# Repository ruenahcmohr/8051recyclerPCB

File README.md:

# 8051recyclerPCB
External memory card for PLCC 8051 OTP processors

PCB designed for recycling OTP PLCC 8051 chips. 

Becasue using the 8051 with external memory burns off most of the ports, I have added two chips that use the external RAM space for an input and output port. Any write to external memory will go to the dedicated output port, and any read from external memory will read the dedicated input port.

(I hope your fine with the in-chip ram :] )

ERATTA:

- The output chip needs to be 74xx374 or another pin compatible chip but sure the heck not the 74xx373
- Oh, maybe those serial leds ought to be active low eh?
- Ya know that trace to that top decoupling cap dunn't need to be only 10 thou.

IMPROVA:

- Could there please be a mark on the common cathode pin of that damn led?
- Could someone please mark the xtal pin for extern clock input?
- Ya know that trace to that top decoupling cap dunn't need to be only 10 thou.
- break out pins 1, 12, 23, 34 to pads incase they need bodge connections
- align the pin 27 connection with VCC for easier bridging to use 2764 roms. (haha wait no, there are only 28 pins)

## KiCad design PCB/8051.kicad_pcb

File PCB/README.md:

# 8051recyclerPCB
External memory card for PLCC 8051 OTP processors

PCB designed for recycling OTP PLCC 8051 chips. 

Becasue using the 8051 with external memory burns off most of the ports, I have added two chips that use the external RAM space for an input and output port. Any write to external memory will go to the dedicated output port, and any read from external memory will read the dedicated input port.

(I hope your fine with the in-chip ram :] )

*not tested yet (oct 2024) *

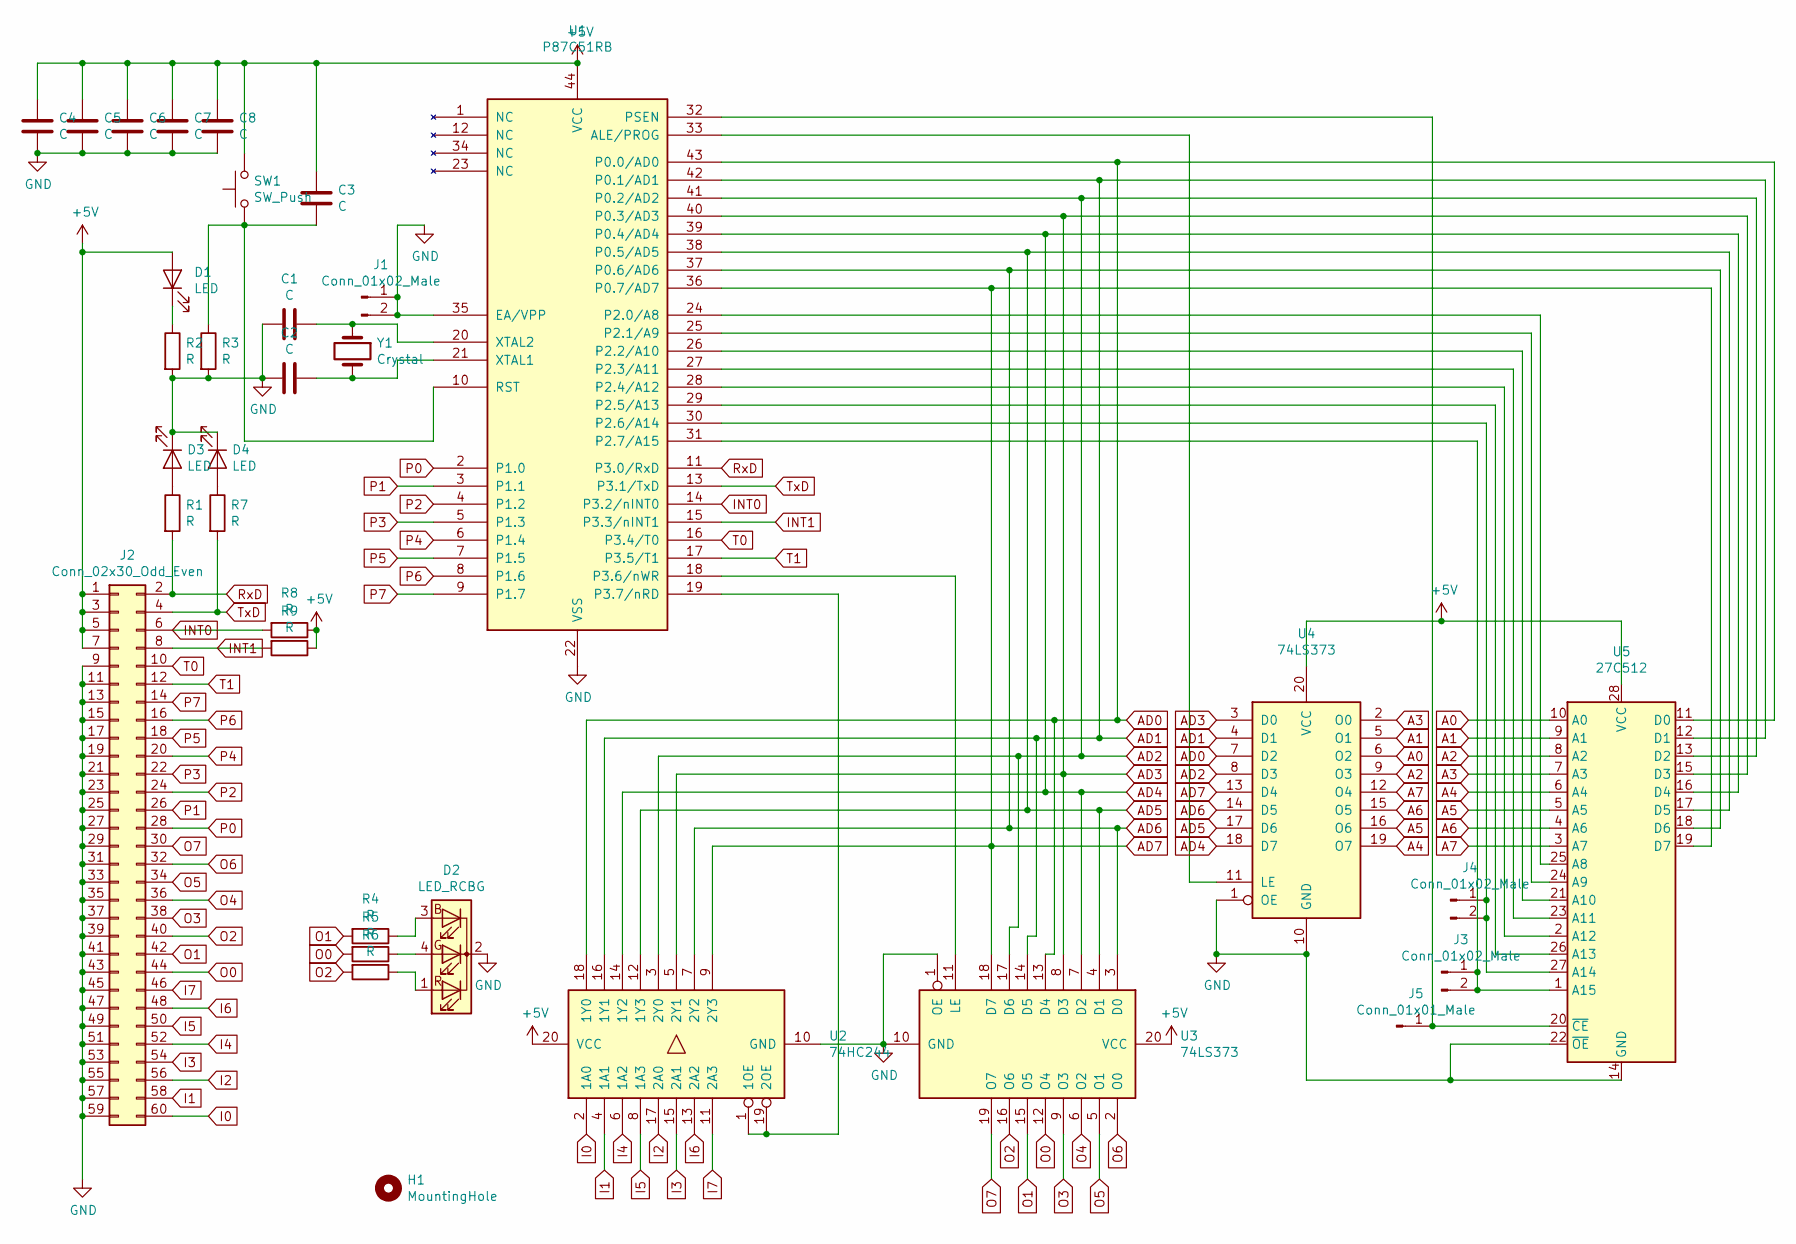
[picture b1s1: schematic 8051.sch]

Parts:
C1, C2: C; C_0805_2012Metric_Pad1.15x1.40mm_HandSolder
C3, C4, C5, C6, C7, C8: C; C_1206_3216Metric_Pad1.42x1.75mm_HandSolder
D1, D3, D4: LED; LED_0805_2012Metric_Pad1.15x1.40mm_HandSolder
D2: LED_RCBG; LED_D5.0mm-4_RGB_Wide_Pins
H1: MountingHole; MountingHole_3.2mm_M3
J1, J3, J4: Conn_01x02_Male; PinSocket_1x02_P2.54mm_Vertical
J2: Conn_02x30_Odd_Even; PinHeader_2x30_P2.54mm_Vertical
J5: Conn_01x01_Male; PinSocket_1x01_P2.54mm_Vertical
R1, R2, R3, R4, R5, R6, R7, R8, R9: R; R_0805_2012Metric_Pad1.15x1.40mm_HandSolder
SW1: SW_Push; SW_PUSH_6mm
U1: P87C51RB; PLCC-44
U2: 74HC244; SOIC-20W_7.5x12.8mm_P1.27mm
U3, U4: 74LS373; SOIC-20W_7.5x12.8mm_P1.27mm
U5: 27C512; DIP-28_W15.24mm
Y1: Crystal; Crystal_HC49-4H_Vertical

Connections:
+5V: C3.1, C4.1, C5.1, C6.1, C7.1, C8.1, D1.2 (A), J2.1, J2.3, J2.5, J2.7, R8.1, R9.1, SW1.1, U1.44 (VCC), U2.20 (VCC), U3.20 (VCC), U4.20 (VCC), U5.28 (VCC)
A0: U4.6 (O2), U5.10 (A0)
A1: U4.5 (O1), U5.9 (A1)
A2: U4.9 (O3), U5.8 (A2)
A3: U4.2 (O0), U5.7 (A3)
A4: U4.19 (O7), U5.6 (A4)
A5: U4.16 (O6), U5.5 (A5)
A6: U4.15 (O5), U5.4 (A6)
A7: U4.12 (O4), U5.3 (A7)
AD0: U1.43 (P0.0/AD0), U2.18 (1Y0), U3.13 (D4), U4.7 (D2), U5.11 (D0)
AD1: U1.42 (P0.1/AD1), U2.16 (1Y1), U3.14 (D5), U4.4 (D1), U5.12 (D1)
AD2: U1.41 (P0.2/AD2), U2.3 (2Y0), U3.17 (D6), U4.8 (D3), U5.13 (D2)
AD3: U1.40 (P0.3/AD3), U2.5 (2Y1), U3.8 (D3), U4.3 (D0), U5.15 (D3)
AD4: U1.39 (P0.4/AD4), U2.14 (1Y2), U3.7 (D2), U4.18 (D7), U5.16 (D4)
AD5: U1.38 (P0.5/AD5), U2.12 (1Y3), U3.4 (D1), U4.17 (D6), U5.17 (D5)
AD6: U1.37 (P0.6/AD6), U2.7 (2Y2), U3.3 (D0), U4.14 (D5), U5.18 (D6)
AD7: U1.36 (P0.7/AD7), U2.9 (2Y3), U3.18 (D7), U4.13 (D4), U5.19 (D7)
GND: C1.2, C2.2, C4.2, C5.2, C6.2, C7.2, C8.2, D2.2 (K), D3.1 (K), D4.1 (K), J1.1, J1.2, J2.9, J2.11, J2.13, J2.15, J2.17, J2.19, J2.21, J2.23, J2.25, J2.27, J2.29, J2.31, J2.33, J2.35, J2.37, J2.39, J2.41, J2.43, J2.45, J2.47, J2.49, J2.51, J2.53, J2.55, J2.57, J2.59, R2.2, R3.2, U1.22 (VSS), U1.35 (EA/VPP), U2.10 (GND), U3.1 (OE), U3.10 (GND), U4.1 (OE), U4.10 (GND), U5.14 (GND), U5.22 (~OE)
I0: J2.60, U2.2 (1A0)
I1: J2.58, U2.4 (1A1)
I2: J2.56, U2.17 (2A0)
I3: J2.54, U2.15 (2A1)
I4: J2.52, U2.6 (1A2)
I5: J2.50, U2.8 (1A3)
I6: J2.48, U2.13 (2A2)
I7: J2.46, U2.11 (2A3)
INT0: J2.6, R8.2, U1.14 (P3.2/nINT0)
INT1: J2.8, R9.2, U1.15 (P3.3/nINT1)
unnamed: C1.1, U1.20 (XTAL2), Y1.1
unnamed: C2.1, U1.21 (XTAL1), Y1.2
unnamed: C3.2, R3.1, SW1.2, U1.10 (RST)
unnamed: D1.1 (K), R2.1
unnamed: D2.1 (RA), R6.1
unnamed: D2.3 (BA), R4.1
unnamed: D2.4 (GA), R5.1
unnamed: D3.2 (A), R1.1
unnamed: D4.2 (A), R7.1
unnamed: J3.1, J3.2, U1.31 (P2.7/A15), U5.1 (A15)
unnamed: J4.1, J4.2, U1.30 (P2.6/A14), U5.27 (A14)
unnamed: J5.1, U1.32 (PSEN), U5.20 (~CE)
unnamed: U1.18 (P3.6/nWR), U3.11 (LE)
unnamed: U1.19 (P3.7/nRD), U2.1 (1OE), U2.19 (2OE)
unnamed: U1.24 (P2.0/A8), U5.25 (A8)
unnamed: U1.25 (P2.1/A9), U5.24 (A9)
unnamed: U1.26 (P2.2/A10), U5.21 (A10)
unnamed: U1.27 (P2.3/A11), U5.23 (A11)
unnamed: U1.28 (P2.4/A12), U5.2 (A12)
unnamed: U1.29 (P2.5/A13), U5.26 (A13)
unnamed: U1.33 (ALE/PROG), U4.11 (LE)
O0: J2.44, R5.2, U3.12 (O4)
O1: J2.42, R4.2, U3.15 (O5)
O2: J2.40, R6.2, U3.16 (O6)
O3: J2.38, U3.9 (O3)
O4: J2.36, U3.6 (O2)
O5: J2.34, U3.5 (O1)
O6: J2.32, U3.2 (O0)
O7: J2.30, U3.19 (O7)
P0: J2.28, U1.2 (P1.0)
P1: J2.26, U1.3 (P1.1)
P2: J2.24, U1.4 (P1.2)
P3: J2.22, U1.5 (P1.3)
P4: J2.20, U1.6 (P1.4)
P5: J2.18, U1.7 (P1.5)
P6: J2.16, U1.8 (P1.6)
P7: J2.14, U1.9 (P1.7)
RxD: J2.2, R1.2, U1.11 (P3.0/RxD)
T0: J2.10, U1.16 (P3.4/T0)
T1: J2.12, U1.17 (P3.5/T1)
TxD: J2.4, R7.2, U1.13 (P3.1/TxD)

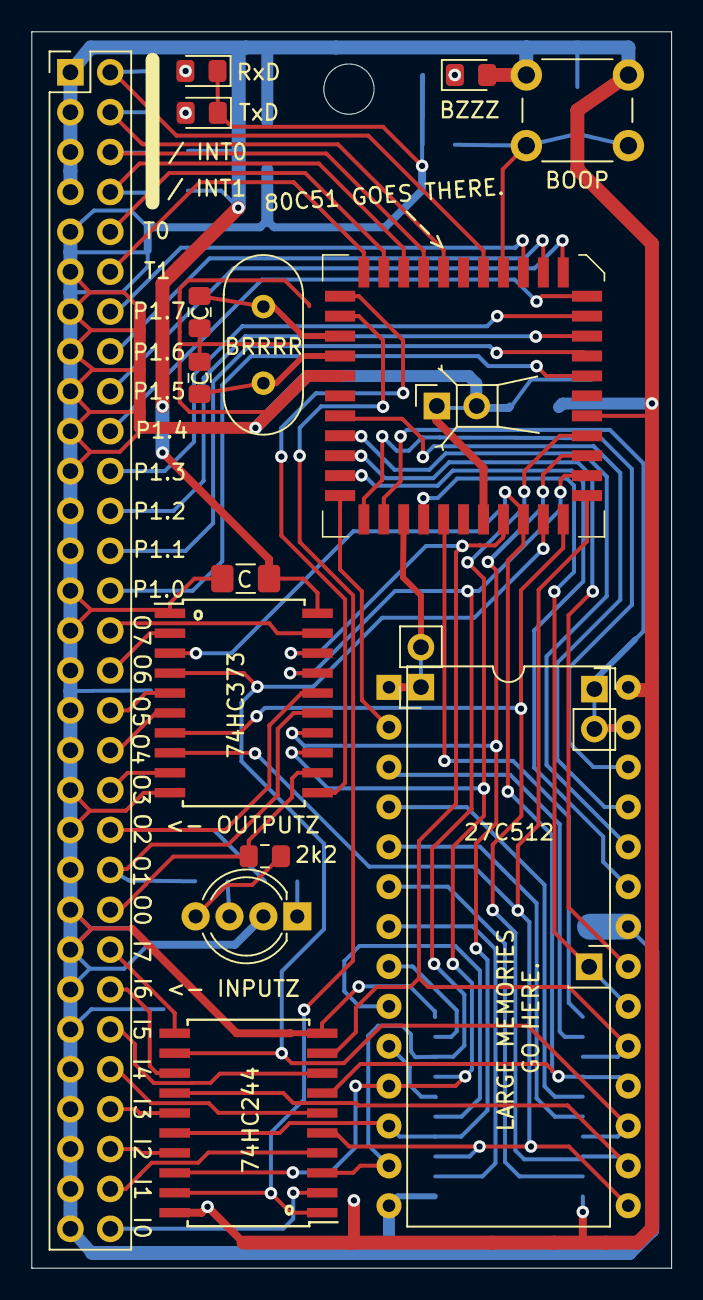
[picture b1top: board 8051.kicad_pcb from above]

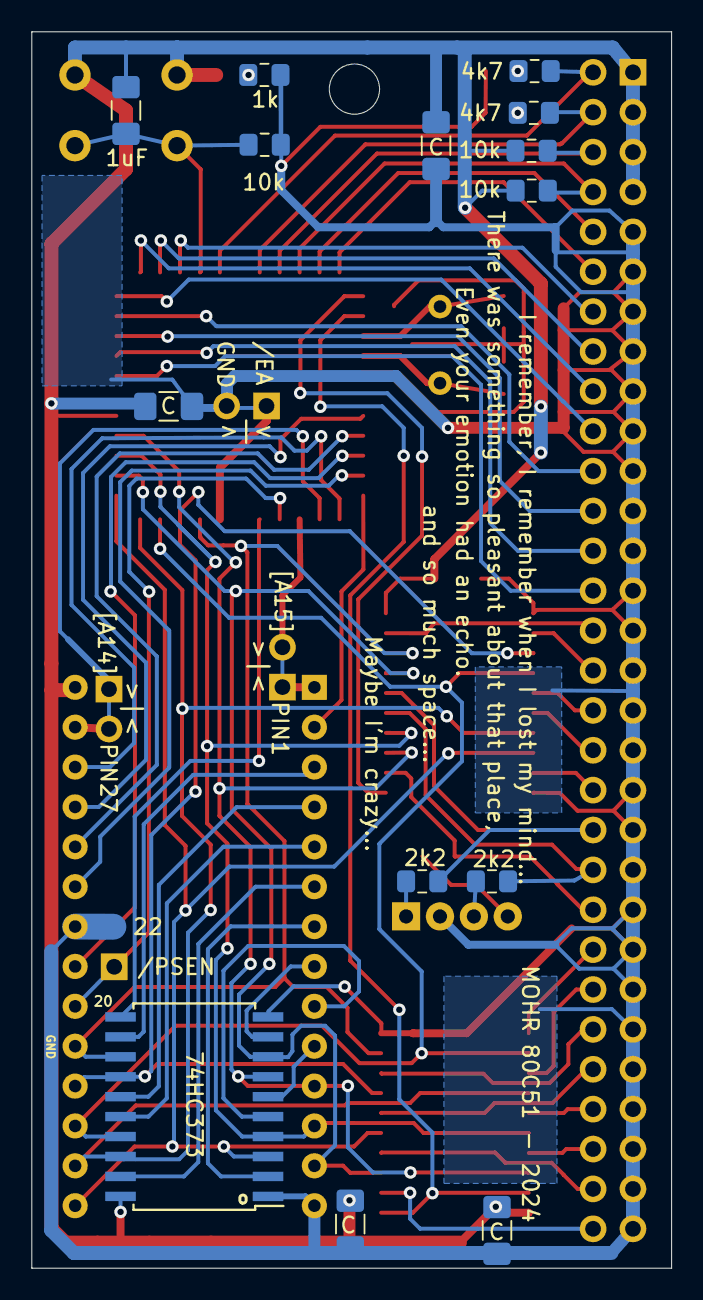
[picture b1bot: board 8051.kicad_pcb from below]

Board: 2 copper layers, 40.8 x 78.8 mm, 34 parts (14 on the bottom side), 69 nets.

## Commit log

2024-11-02 adding files
2024-11-18 folders and adding example source
2024-11-18 oops
2024-11-18 Readme update
2025-01-12 Update README.md
    updated improvement list
2025-01-12 Update README.md
    improva
